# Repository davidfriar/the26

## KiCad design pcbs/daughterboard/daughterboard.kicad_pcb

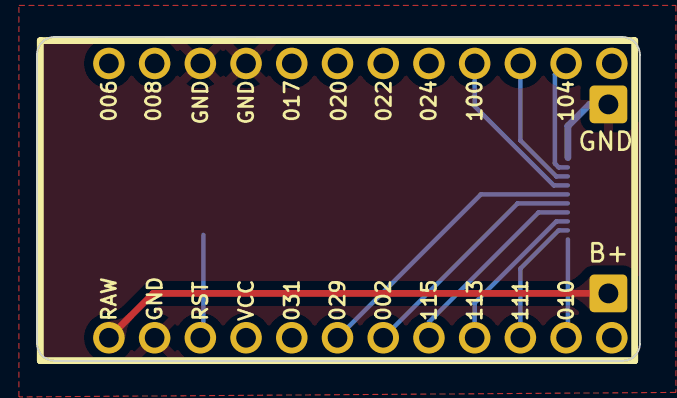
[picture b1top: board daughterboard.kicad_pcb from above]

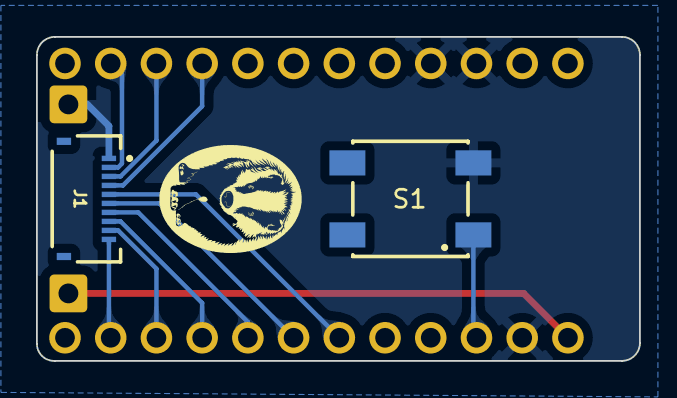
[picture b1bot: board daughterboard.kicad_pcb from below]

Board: 2 copper layers, 33.5 x 18.0 mm, 5 parts (2 on the bottom side), 12 nets.

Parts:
B+: B+; SolderWire-0.5sqmm_1x01_D0.9mm_OD2.1mm
GND: Conn_01x01; SolderWire-0.5sqmm_1x01_D0.9mm_OD2.1mm
J1: Conn_01x10_Socket; GCT_FFC2B28-10-G
S1: 430471035826
U1: nice_nano

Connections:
B+: B+.1, U1.24 (BATIN/P0.04)
Column1: J1.5, U1.19 (AIN5/P0.29)
Column2: J1.6, U1.18 (AIN0/P0.02)
Column3: J1.7, U1.17 (P1.15)
Column4: J1.8, U1.16 (P1.13)
Column5: J1.9, U1.15 (P1.11)
Column6: J1.10, U1.14 (NFC2/P0.10)
GND: GND.1, J1.1, S1.3, U1.3 (GND), U1.4 (GND), U1.23 (GND)
unnamed: S1.1, U1.22 (RST)
Row1: J1.2, U1.11 (P1.04)
Row2: J1.3, U1.10 (P0.11)
Row3: J1.4, U1.9 (P1.00)

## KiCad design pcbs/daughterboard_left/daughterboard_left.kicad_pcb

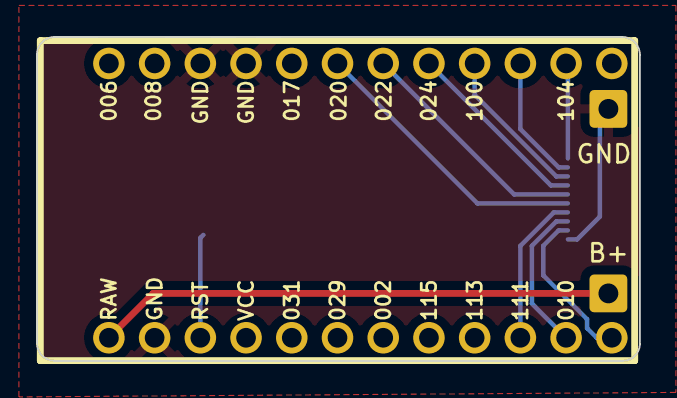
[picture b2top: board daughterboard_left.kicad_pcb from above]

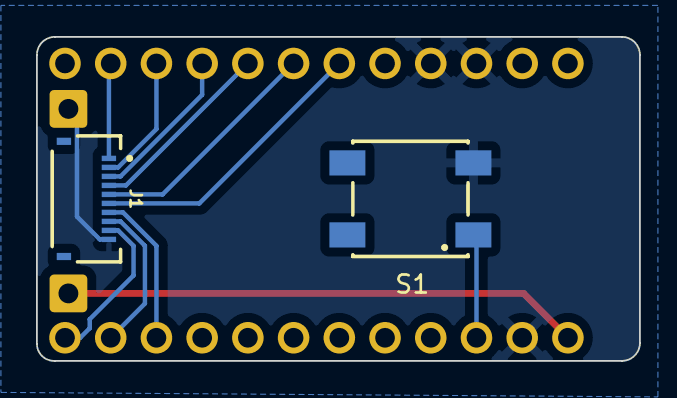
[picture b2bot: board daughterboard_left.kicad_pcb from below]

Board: 2 copper layers, 33.5 x 18.0 mm, 5 parts (2 on the bottom side), 12 nets.

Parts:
B+: Conn_01x01; SolderWire-0.5sqmm_1x01_D0.9mm_OD2.1mm
GND: Conn_01x01; SolderWire-0.5sqmm_1x01_D0.9mm_OD2.1mm
J1: Conn_01x10_Socket; GCT_FFC2B28-10-G
S1: 430471035826
U1: nice_nano

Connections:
B+: B+.1, U1.24 (BATIN/P0.04)
Column1: J1.1, U1.11 (P1.04)
Column2: J1.2, U1.10 (P0.11)
Column3: J1.3, U1.9 (P1.00)
Column4: J1.4, U1.8 (P0.24)
Column5: J1.5, U1.7 (P0.22)
Column6: J1.6, U1.6 (P0.20)
GND: GND.1, J1.10, S1.3, U1.3 (GND), U1.4 (GND), U1.23 (GND)
unnamed: S1.1, U1.22 (RST)
Row1: J1.9, U1.13 (NFC1/P0.09)
Row2: J1.8, U1.14 (NFC2/P0.10)
Row3: J1.7, U1.15 (P1.11)

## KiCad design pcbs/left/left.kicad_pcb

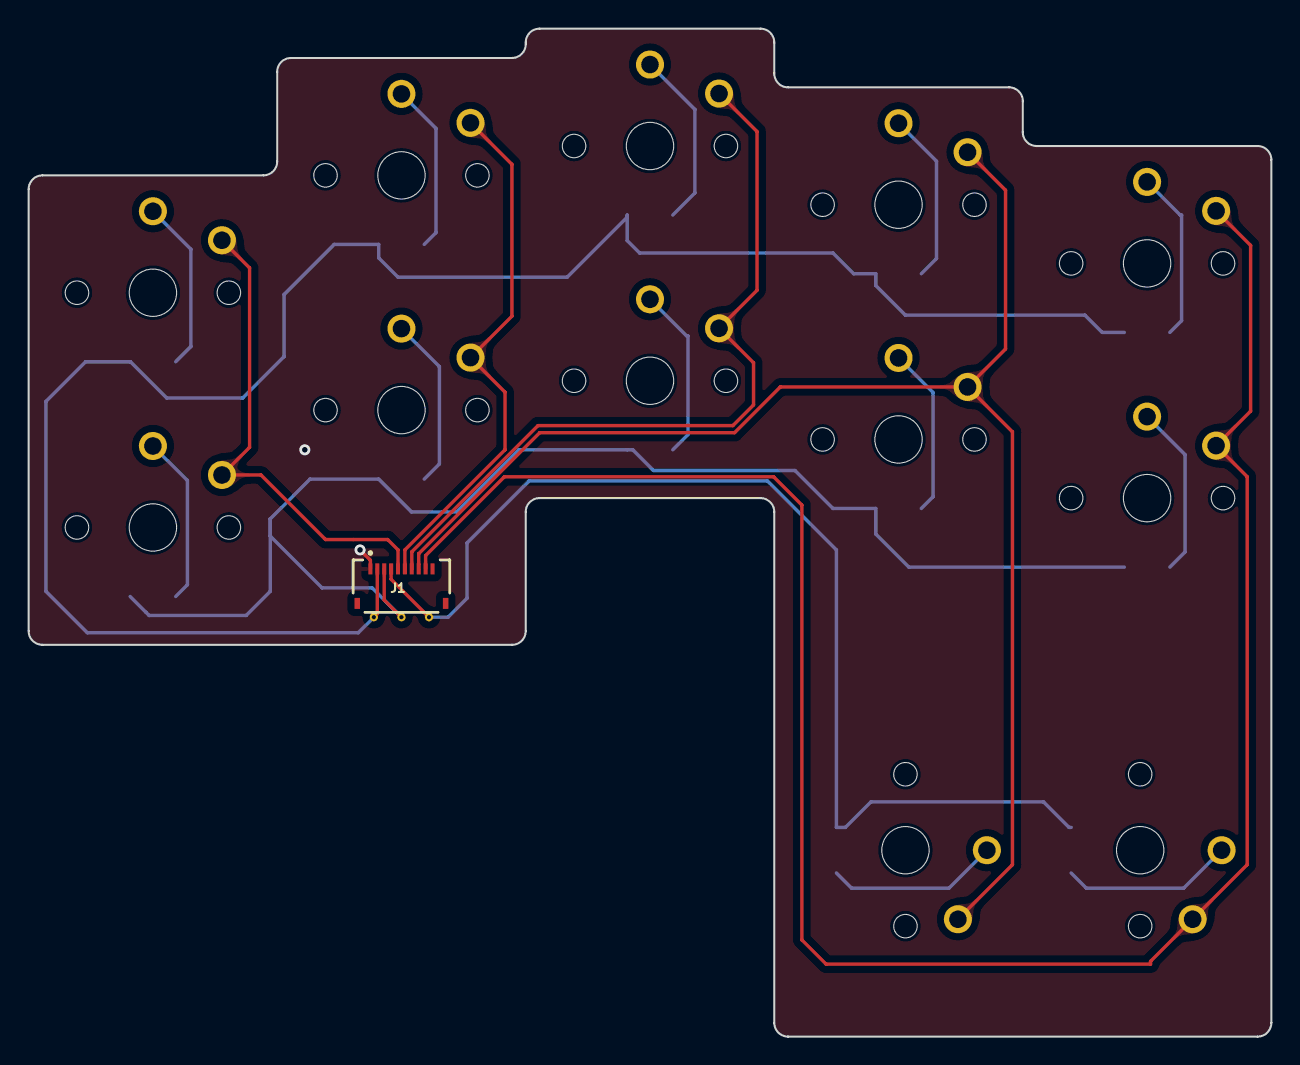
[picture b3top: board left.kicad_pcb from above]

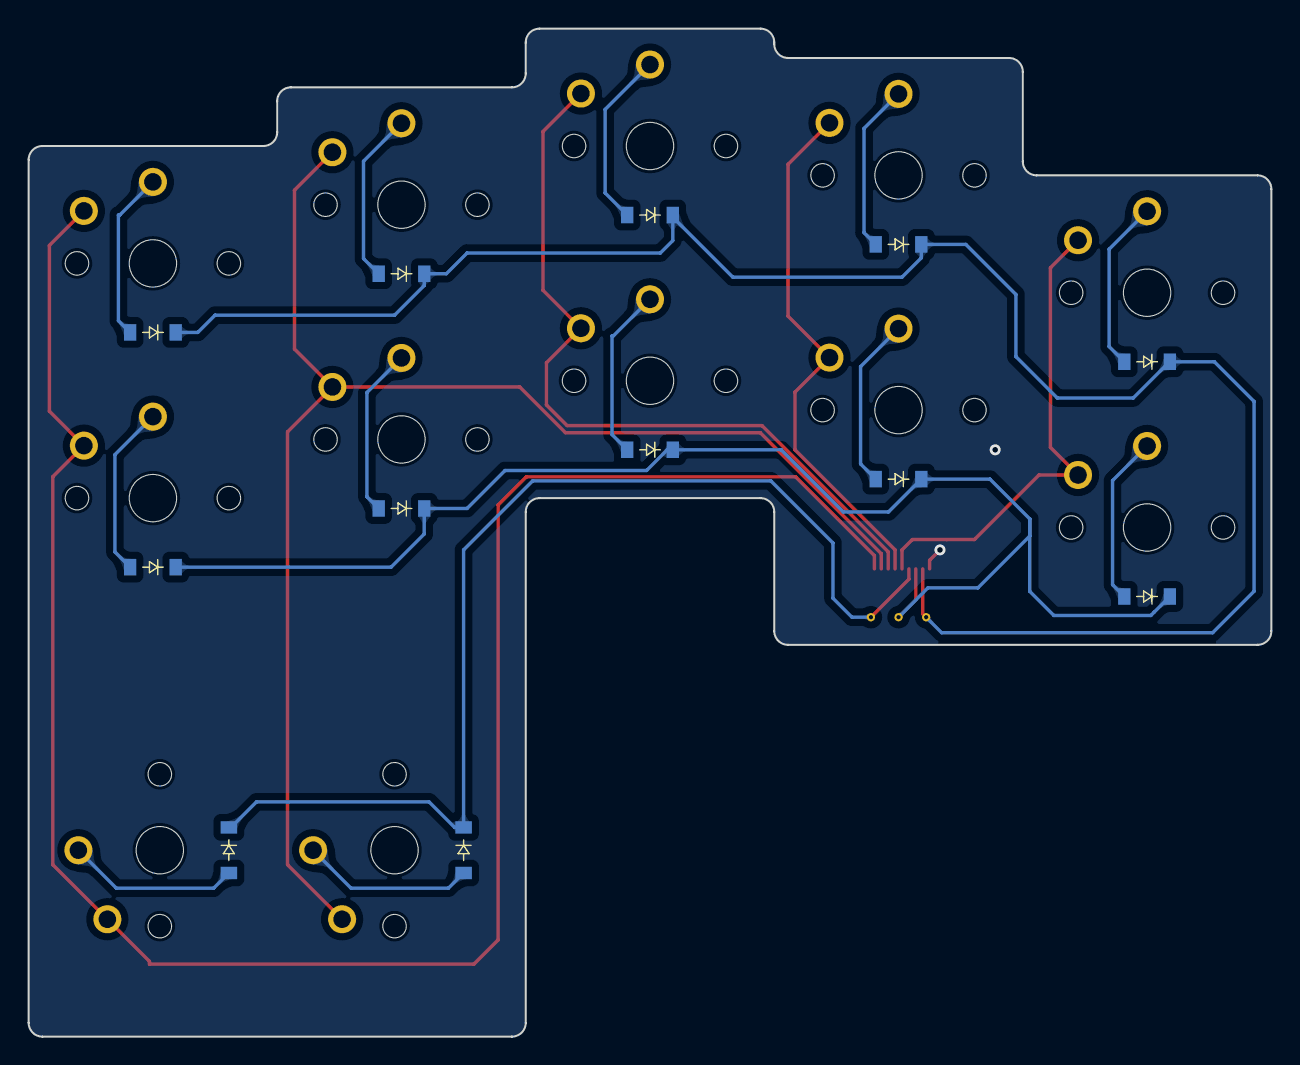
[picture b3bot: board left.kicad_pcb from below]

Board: 2 copper layers, 90.0 x 73.0 mm, 28 parts (12 on the bottom side), 20 nets.

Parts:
D1, D2, D3, D4, D5, D6, D7, D8, D9, D10, D11, D12: ComboDiode
J1: Conn_01x10_Socket; Molex2004850410
S1, S2, S3, S4, S5, S6, S7, S8, S9, S10, S11, S12: PG1350
_1, _2, _3: VIA-0.6mm

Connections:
C1: J1.5, S1.1, S2.1
C2: J1.6, S3.1, S4.1
C3: J1.7, S5.1, S6.1
C4: J1.8, S7.1, S8.1, S11.1
C5: J1.9, S9.1, S10.1, S12.1
R1: D2.1, D4.1, D6.1, D8.1, D10.1, J1.2, _1.1
R2: D1.1, D3.1, D5.1, D7.1, D9.1, J1.3, _2.1
R3: D11.1, D12.1, J1.4, _3.1
index_bottom: D7.2, S7.2
index_top: D8.2, S8.2
inner_bottom: D9.2, S9.2
inner_thumb: D12.2, S12.2
inner_top: D10.2, S10.2
middle_bottom: D5.2, S5.2
middle_top: D6.2, S6.2
outer_thumb: D11.2, S11.2
pinky_bottom: D1.2, S1.2
pinky_top: D2.2, S2.2
ring_bottom: D3.2, S3.2
ring_top: D4.2, S4.2

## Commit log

2024-02-26 remove thumber keys, rotate and realign thumb keys
2024-03-24 lots of changes
2024-04-01 more changes
2024-04-01 add new reset switch
2024-04-01 kicad gitignore
2024-04-01 single daughterboard
2024-04-03 plate and pcb finished
2024-04-03 add mising image
2024-04-03 project name change
2024-04-07 case updates and pcb tweaks
2024-04-16 case updates
2024-05-12 ready for first print
2024-05-12 clearance for bottom of daughterboard
